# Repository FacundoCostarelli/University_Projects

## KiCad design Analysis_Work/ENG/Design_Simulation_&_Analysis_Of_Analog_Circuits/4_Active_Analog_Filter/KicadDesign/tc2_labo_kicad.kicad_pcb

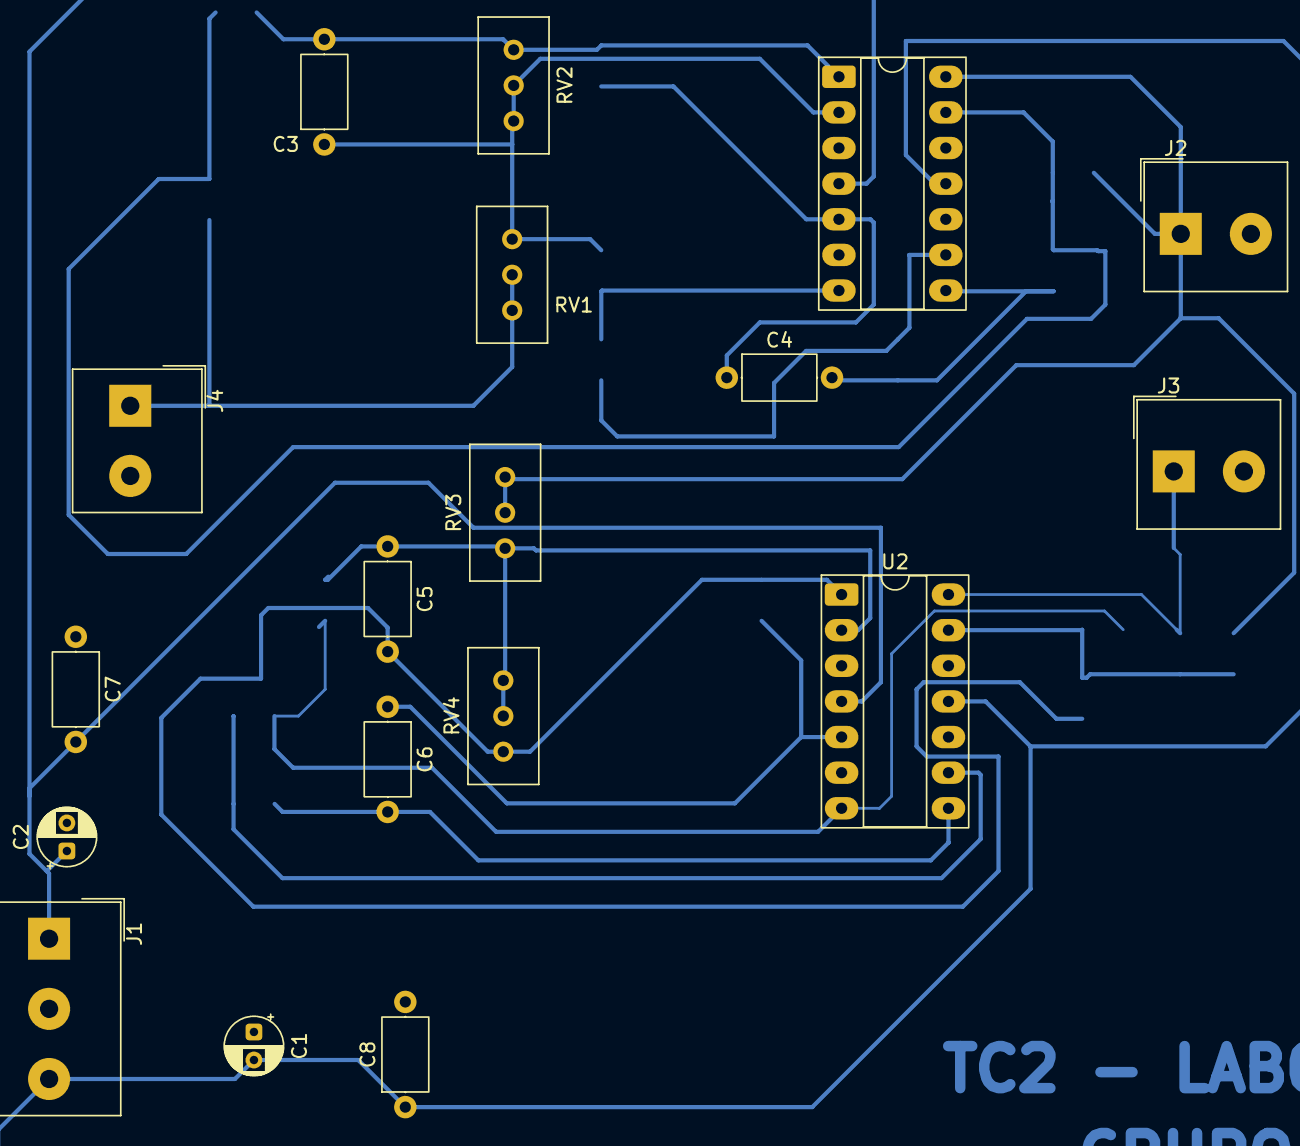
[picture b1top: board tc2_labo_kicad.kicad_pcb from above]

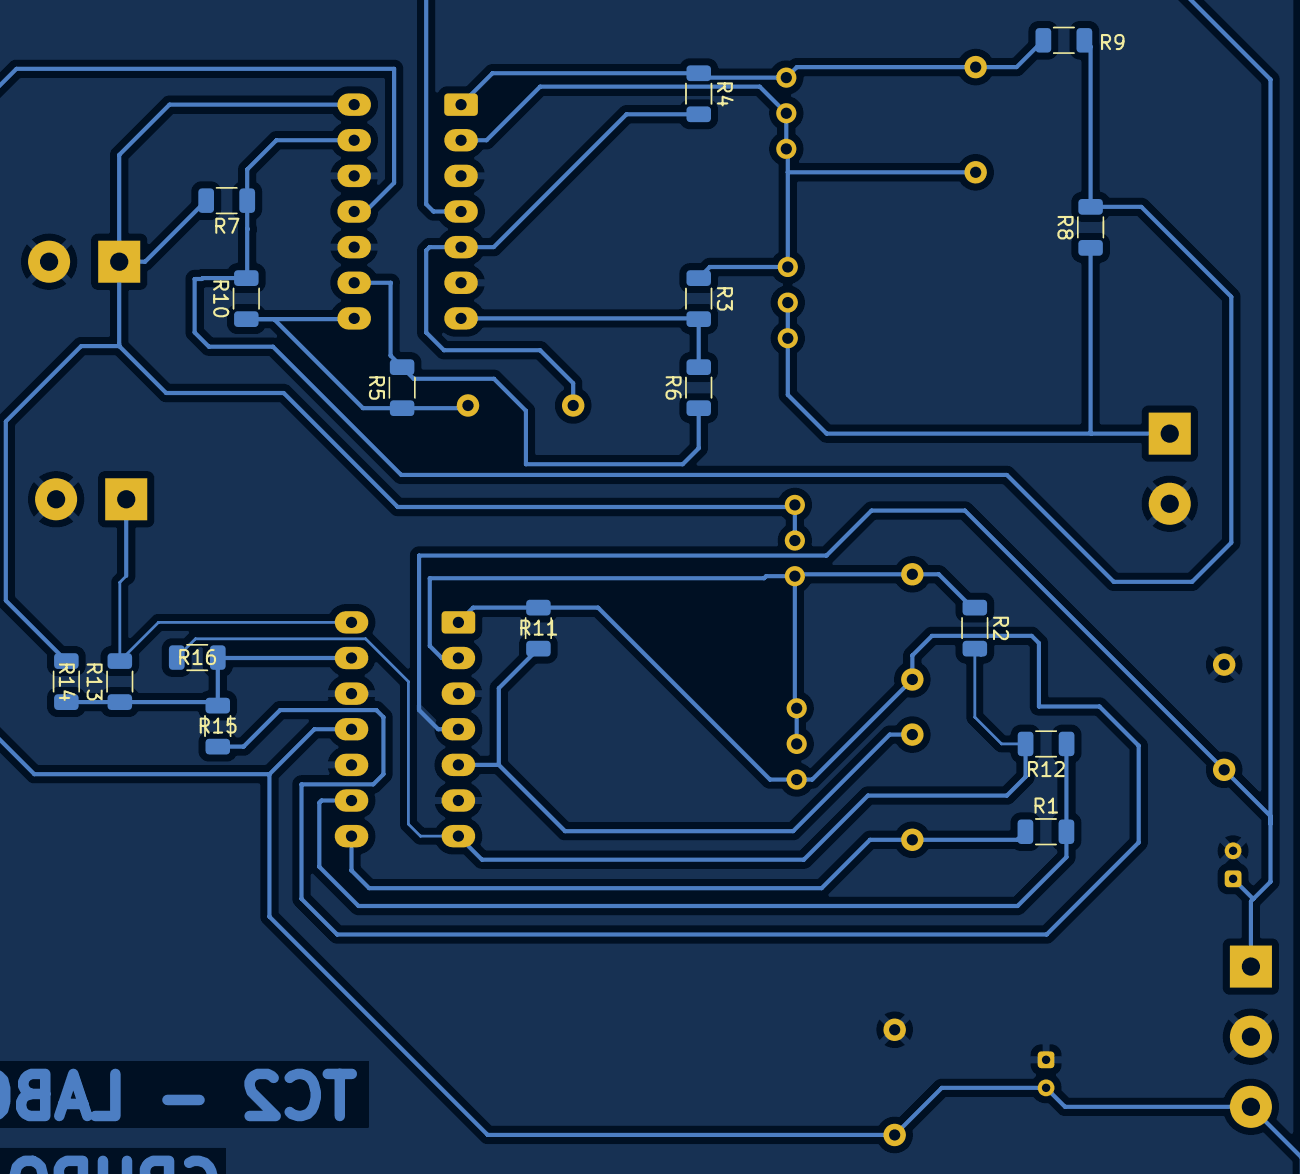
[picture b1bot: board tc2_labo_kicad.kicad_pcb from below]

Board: 2 copper layers, 34 parts (16 on the bottom side), 20 nets.

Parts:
C1, C2: C_Polarized; CP_Radial_D4.0mm_P2.00mm
C3, C4, C5, C6, C7, C8: 100n; C_Axial_L5.1mm_D3.1mm_P7.50mm_Horizontal
J1: Screw_Terminal_01x03; Altech_AK100_1x03_P5.00mm
J2, J3, J4: Screw_Terminal_01x02; Altech_AK100_1x02_P5.00mm
R1, R5, R6, R12, R16: 2k2; R_1206_3216Metric
R2, R11: 220; R_1206_3216Metric
R3, R4: 390; R_1206_3216Metric
R7, R8, R13, R14: 1k; R_1206_3216Metric
R9: 2k; R_1206_3216Metric
R10: 1K2; R_1206_3216Metric
R15: 1k8; R_1206_3216Metric
RV1, RV2, RV3, RV4: R_Potentiometer; Potentiometer_Bourns_3296W_Vertical
U1, U2: LM324; DIP-14_W7.62mm_Socket_LongPads

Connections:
+VCC: C2.1, C7.2, J1.1, U1.4 (V+), U2.4 (V+)
-VCC: C1.2, C8.1, J1.3, U1.11 (V-), U2.11 (V-)
-VL1: C4.2, R5.1, R10.1, U1.8
GND: C1.1, C2.2, C7.1, C8.2, J1.2, J2.2, J3.2, J4.2, U1.3 (+), U1.6 (-), U1.10 (+), U1.12 (+), U2.3 (+), U2.6 (-), U2.10 (+), U2.12 (+)
unnamed: C6.2, R1.1, U2.8
unnamed: C3.1, R3.1, RV1.3, RV2.1, RV2.2, U1.2 (-)
unnamed: C4.1, R4.2, U1.5 (+)
unnamed: R5.2, R6.1, U1.9 (-)
unnamed: R7.1, R8.2, R9.2, R10.2, U1.13 (-)
unnamed: C5.1, R2.1, RV3.3, RV4.1, RV4.2, U2.2 (-)
unnamed: C6.1, R11.2, U2.5 (+)
unnamed: R1.2, R12.1, U2.9 (-)
unnamed: R13.1, R14.2, R15.2, R16.2, U2.13 (-)
VB1: C3.2, R4.1, R9.1, RV2.3, U1.1
VB2: C5.2, R11.1, R15.1, RV4.3, U2.1
VL1: R3.2, R6.2, U1.7
VL2: R2.2, R12.2, R16.1, U2.7
Vi: J4.1, R8.1, RV1.1, RV1.2
Vo1: J2.1, R7.2, R14.1, RV3.1, RV3.2, U1.14
Vo2: J3.1, R13.2, U2.14

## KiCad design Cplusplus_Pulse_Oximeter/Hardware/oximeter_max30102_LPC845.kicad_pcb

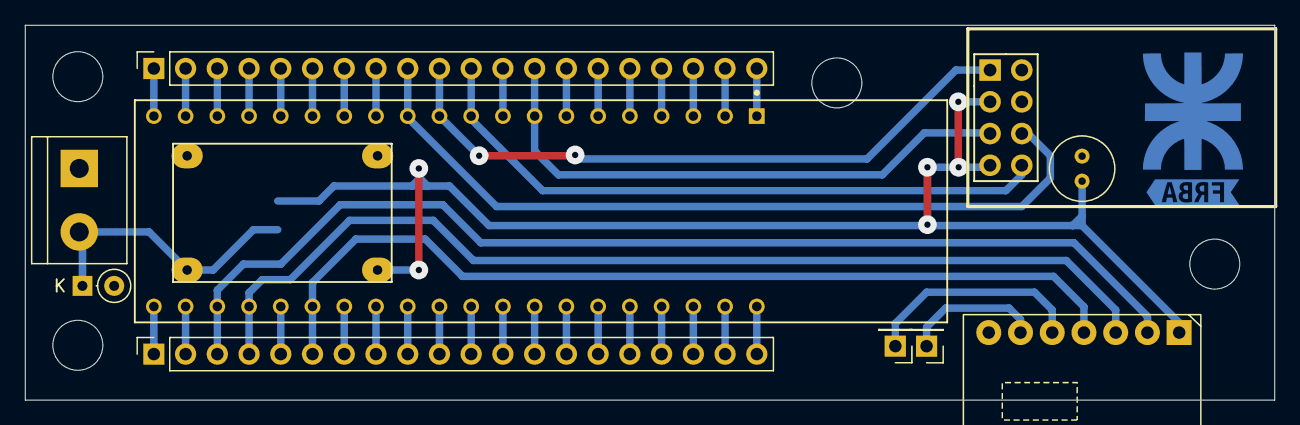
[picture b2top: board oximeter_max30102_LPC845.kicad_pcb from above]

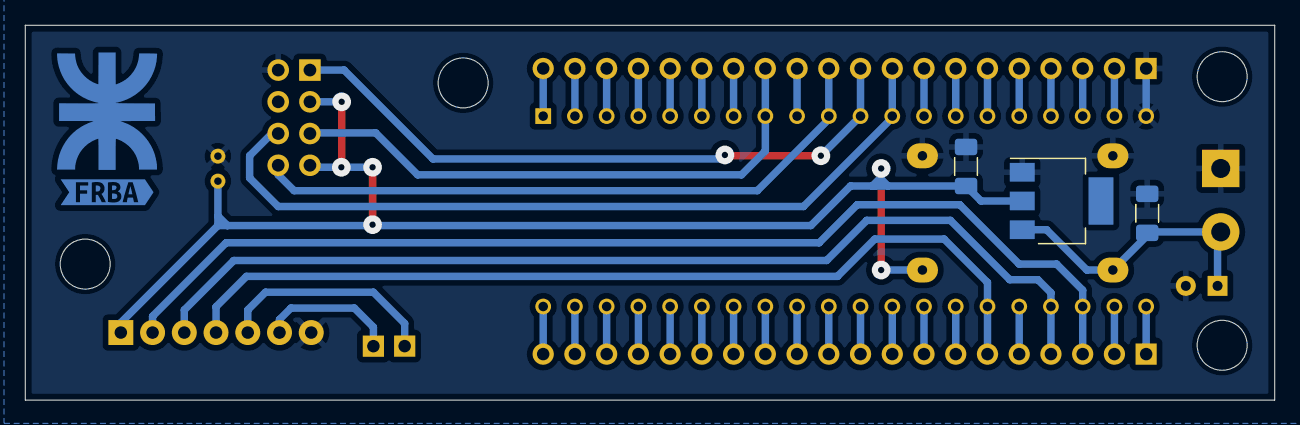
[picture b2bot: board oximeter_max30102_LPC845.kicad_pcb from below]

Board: 2 copper layers, 100.0 x 30.0 mm, 19 parts (4 on the bottom side), 44 nets.

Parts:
C1, C2: C; C_1206_3216Metric_Pad1.33x1.80mm_HandSolder
C3: C; C_Radial_D5.0mm_H7.0mm_P2.00mm
D1: D; D_DO-35_SOD27_P2.54mm_Vertical_KathodeUp
H1, H2, H3, H4: MountingHole; MountingHole_4mm
J1: VIN; TerminalBlock_bornier-2_P5.08mm
J7, J9: Conn_01x20_Socket; PinSocket_1x20_P2.54mm_Vertical
MD1: LPC845-BRK; NXP_Semiconductors-LPC845-BRK-MFG
TP1, TP2: TestPoint; PinHeader_1x01_P2.54mm_Vertical
U1: MAX30102-BRK
U2: ESP-01v090; ESP-01
U3: Mini360; Mini360_step-down
U4: AMS1117-3.3; SOT-223-3_TabPin2
kibuzzard-67073386: G***; kibuzzard-67073386

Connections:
+3V3: C2.1, C3.1, U1.1 (VIN), U2.3 (CH_PD), U2.7 (VCC), U3.4 (OUT+), U4.2 (VO)
/I2C_SCL: J9.3, MD1.23 (PIO0_10), U1.2 (SCL)
/I2C_SDA: J9.4, MD1.24 (PIO0_11), U1.3 (SDA)
/LED_B: J9.10, MD1.30 (PIO1_1/BLUE_LED)
/LED_G: J9.11, MD1.31 (PIO1_0/GREEN_LED)
/LED_R: J9.9, MD1.29 (PIO1_2/RED_LED)
/PIO0_0: J9.19, MD1.39 (PIO0_00)
/PIO0_1: J9.18, MD1.38 (PIO0_01)
/PIO0_2: J9.17, MD1.37 (PIO0_02/SWDIO)
/PIO0_3: J9.16, MD1.36 (PIO0_03/SWCLK)
/PIO0_4: J9.15, MD1.35 (PIO0_04/USER)
/PIO0_5: J7.12, MD1.9 (PIO0_05/~RESET)
/PIO0_5b: J9.14, MD1.34 (PIO0_05/~RESET)
/PIO0_6: J9.13, MD1.33 (PIO0_06)
/PIO0_7: J9.12, MD1.32 (PIO0_07/ADC/POT)
/PIO0_8: J7.2, MD1.19 (PIO0_08)
/PIO0_8b: J9.1, MD1.21 (PIO0_08)
/PIO0_9: J7.3, MD1.18 (PIO0_09)
/PIO0_9b: J9.2, MD1.22 (PIO0_09)
/PIO0_12: J9.5, MD1.25 (PIO0_12/ISP)
/PIO0_14: J9.7, MD1.27 (PIO0_14)
/PIO0_15: J9.8, MD1.28 (PIO0_15)
/PIO0_16: J7.20, MD1.1 (PIO0_16)
/PIO0_17: J7.19, MD1.2 (PIO0_17)
/PIO0_18: J7.18, MD1.3 (PIO0_18)
/PIO0_19: J7.17, MD1.4 (PIO0_19)
/PIO0_20: J7.16, MD1.5 (PIO0_20)
/PIO0_21: J7.15, MD1.6 (PIO0_21)
/PIO0_22: J7.14, MD1.7 (PIO0_22)
/PIO0_24: J7.11, MD1.10 (PIO0_24/TXD), U2.8 (URXD)
/PIO0_25: J7.10, MD1.11 (PIO0_25/RXD), U2.1 (UTXD)
/PIO0_27: J7.8, MD1.13 (PIO0_27)
/PIO0_28: J7.7, MD1.14 (PIO0_28)
/PIO0_29: J7.6, MD1.15 (PIO0_29)
/PIO0_30: J7.5, MD1.16 (PIO0_30)
/PIO0_31: J7.4, MD1.17 (PIO0_31)
/PRG_MODE: J7.9, MD1.12 (PIO0_26), U2.6 (GPIO0)
/RST: J7.13, MD1.8 (PIO0_23), U2.5 (RST)
/VDD: J9.20, MD1.40 (VDD)
/~INT: J9.6, MD1.26 (PIO0_13), U1.4 (INT)
GND: C1.2, C2.2, C3.2, D1.2 (A), J1.1, J7.1, MD1.20 (GND), U1.7 (GND), U2.2 (GND), U3.1 (IN-), U3.3 (OUT-), U4.1 (GND)
unnamed: C1.1, D1.1 (K), J1.2, U3.2 (IN+), U4.3 (VI)
unnamed: TP1.1, U1.5 (IRD)
unnamed: TP2.1, U1.6 (RD)

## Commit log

2024-12-30 Pulse Oximeter Proyect
2024-12-30 Deleting files
2025-01-04 Adding Documents,Reports,Datasheets,etc
2025-01-04 Adding README_ES.md file
2025-02-14 Adding Microcontroller files
2025-02-14 Adding README_ESP.md Markdown format
2025-02-16 Adding README_ESP.md modified authors and deleting microcontroller files
2025-02-16 Adding updated microcontroller files
2025-03-02 Deleting GUI QT files
2025-03-02 Adding QT files -> GUI working
2025-03-03 Modifying README_ES.md file
2025-03-05 Deleting GUI_Pulse_Oximeter files
2025-03-05 Adding modified GUI_Pulse_Oximeter files
2025-03-08 Adding modified README_ES.md file and README_ENG.md modifications
2025-03-09 Adding modified README_ES.md file and README_ENG.md modifications and images for QT folder
2025-03-12 Modifying Technial Report in Spanish And English
2025-03-12 README_ESṔ & README_ENG
2025-03-17 Adding new proyect --> Graphics_Menu & files attached
2025-03-19 Adding new proyects
2025-03-22 Modifying C file
2025-03-24 Modifying C file and adding README_ESP & README_ENG
2025-03-25 Modifying & Adding PDFs in Documents_And_References
2025-03-25 Modifying README_ENG PulseOximeter
2025-03-25 Modifying README_ESP & README_ENG BMP_Image_Processing Proyect
2025-03-26 Adding Research_And_Anaysis_Work files and docs
2025-03-26 Adding new MATLAB docs & Reasearch files
2025-04-02 Changing folder nama
2025-04-02 deleting file
2025-04-08 adding equalizer project
2025-05-07 adding equalizer project files
2025-10-06 Uploading some new folders
2025-10-07 Uploading some new files in BioEngineering_DigitalSignalProcessing folder
2025-10-07 Uploading a new folder Python_BioSignals_Analysis_&_Processing
2025-12-06 Subo README_ESP & README_ENG para MATLAB_Signal_DTMF_Signal_Encoding_&_Decoding & MATLAB_Signal_Analysis_&_Processing project
2025-12-20 Subo README_ESP & README_ENG para VHDL_ProcessorDesign_Project y subo codigos del proyecto. Subo los codigos de VHDL_Mini_Projects
2025-12-20 Subo VHDL_Mini_Project files & VHDL_Multiple_Purpose_Library
2026-03-05 Uploading new files for Python_BioSignals_Analysis_&_Processing
2026-03-13 Uploading Research_&_Magazine_Publishing files for Preliminary_Assessment_of_a_Multisite_SpO₂_Probe_for_Clinical_Application
2026-03-13 Uploading Analysis_Work files
2026-03-15 Deleting one longer file
2026-03-16 Uploading one new folder
2026-03-17 Uploading Diseño_Simulación_&_Análisis_De_Circuitos_Analógicos with sub folders
2026-03-17 Uploading new folders and files related to Analog Circuits Design and Analysis
2026-03-18 Backup: state before folder reorganization (2026-03-18)
2026-03-18 Reorganize: clean folder structure, bilingual READMEs, shortened paths
2026-03-18 Add bilingual ESP-ENG comments to all library files
2026-03-19 docs: Professional Doxygen overhaul for all 12 library modules - Created 12 new .h headers with @param/@return/@example docs - Rewrote 25+ .c files with bilingual [ESP]/[ENG] comments - Fixed C issue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
2026-03-19 refactor: Add main.c examples, ServerClient portable lib, and cleanup build artifacts
2026-03-20 Refactor: Add bilingual Doxygen comments, rename files and folders to English, and translate PDF instructions to Markdown
2026-03-22 Adding some screenshots of the code
2026-03-24 Update tp2.m to save audio and graphs and add gitignore for outputs
2026-03-24 Allow tracking of outputs by removing gitignore
